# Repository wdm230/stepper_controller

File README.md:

# Syringe Pump Controller Project

This project provides a complete solution for building a cost-effective syringe pump controller. It includes a C# GUI application for controlling the pump, PCB designs, circuit schematics, 3D printed components, and Arduino code for the ESP32 microcontroller.

## Table of Contents

1. [Introduction](#introduction)
2. [Project Structure](#project-structure)
3. [C# GUI Application](#c-gui-application)
4. [PCB Design](#pcb-design)
5. [Circuit and PCB Files](#circuit-and-pcb-files)
6. [3D Models](#3d-models)
7. [Arduino Code](#arduino-code)
8. [Documentation](#documentation)
9. [How to Contribute](#how-to-contribute)
10. [License](#license)

## Introduction

This project is focused on developing an affordable syringe pump controller that can be assembled with readily available components. The controller is built around an ESP32 microcontroller, with a C# application providing a user-friendly interface. The hardware includes a custom PCB and 3D-printed components to house the electronics and mechanical parts.

## Project Structure

The repository is organized as follows:

- **GUI/**: C# codebase for the graphical user interface (GUI) application.
- **PCB/**: Gerber files for manufacturing the printed circuit board (PCB).
- **circuit_board/**: KiCad project files, including the circuit schematic and PCB layout.
- **models/**: 3D models for printing the syringe pump housing and related parts.
- **syringe_pump_controller.ino**: Arduino sketch for the ESP32 microcontroller, handling motor control and communication with the GUI.
- **docs.pdf**: Comprehensive documentation covering project setup, usage, and technical details.

## C# GUI Application

The C# GUI application provides control over the syringe pump's operation. Key features include:

- Configuring syringe diameter, fluid volume, and flow rate.
- Real-time motor control, including start, stop, and jog functions.
- Monitoring of current syringe position, motor RPM, and estimated time to empty.

The application is developed in C# using .NET, and the source code is located in the `GUI` directory. It can be built using Visual Studio or the .NET CLI.

## PCB Design

The custom PCB integrates the ESP32 microcontroller with the motor driver and other essential components. The Gerber files in the `PCB` directory are ready for submission to any PCB fabrication service.

## Circuit and PCB Files

The `circuit_board` directory contains the KiCad files for the project, including the full circuit schematic and PCB layout. These files are intended for users who need to modify the circuit design or manufacture their own PCBs.

## 3D Models

The `models` directory includes STL files for 3D printing the syringe pump housing and other mechanical parts. These models are designed to fit standard syringe sizes and the custom PCB.

## Arduino Code

The `syringe_pump_controller.ino` file is the Arduino code that runs on the ESP32. This code handles:

- Motor control, including speed, direction, and position tracking.
- Communication with the C# GUI over serial.
- Homing and emergency stop functions.

The code is designed to be flexible and can be modified for different hardware configurations.

## Documentation

Detailed documentation is available in `docs.pdf`, covering all aspects of the project, from hardware assembly to software configuration. It also includes troubleshooting tips, among other things.

## How to Contribute

Contributions are welcome. If you have improvements or fixes, please fork the repository, make your changes, and submit a pull request. Whether it's code enhancements, bug fixes, or documentation updates, your contributions are appreciated.

## License

This project is licensed under the MIT License. See the `LICENSE` file for more details.

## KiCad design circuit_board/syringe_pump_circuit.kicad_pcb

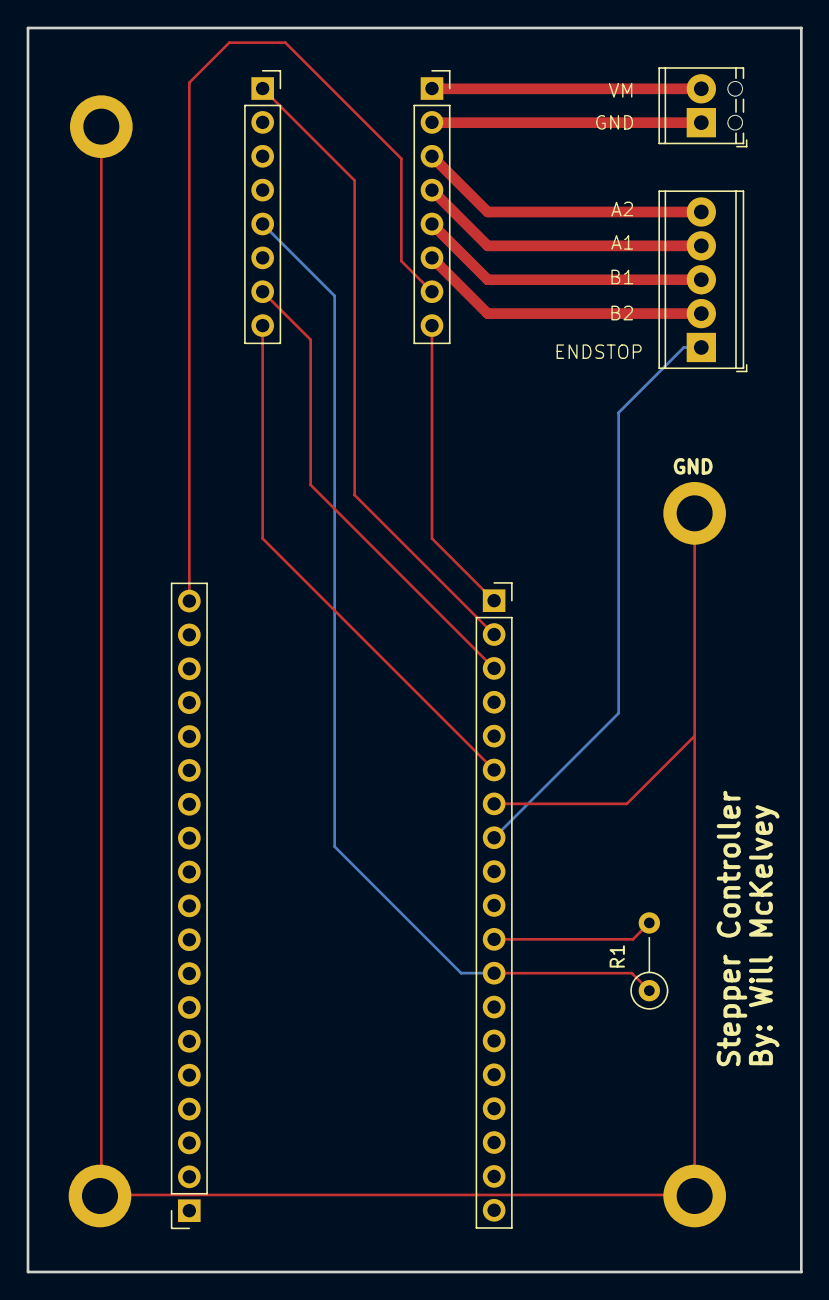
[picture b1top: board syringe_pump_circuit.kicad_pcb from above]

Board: 2 copper layers, 58.0 x 93.3 mm, 11 parts (0 on the bottom side), 15 nets.

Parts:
H1, H2, H3, H4: MountingHole_Pad; MountingHole_2.7mm_M2.5_DIN965_Pad
J1, J2: Conn_01x19_Socket; PinSocket_1x19_P2.54mm_Vertical
J3, J4: Conn_01x08_Socket; PinSocket_1x08_P2.54mm_Vertical
J5: Screw_Terminal_01x05; TerminalBlock_Phoenix_MPT-0,5-5-2.54_1x05_P2.54mm_Horizontal
J6: Screw_Terminal_01x02; TerminalBlock_Phoenix_MPT-0,5-2-2.54_1x02_P2.54mm_Horizontal
R1: 1000; R_Axial_DIN0207_L6.3mm_D2.5mm_P5.08mm_Vertical

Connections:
unnamed: J1.19, J3.7
unnamed: J2.1, J3.8
unnamed: J2.2, J4.1
unnamed: J2.3, J4.7
unnamed: J2.6, J4.8
unnamed: H1.1, H2.1, H3.1, H4.1, J2.7
unnamed: J2.8, J5.1
unnamed: J2.11, R1.2
unnamed: J2.12, J4.5, R1.1
unnamed: J3.1, J6.2
unnamed: J3.2, J6.1
unnamed: J3.3, J5.5
unnamed: J3.4, J5.4
unnamed: J3.5, J5.3
unnamed: J3.6, J5.2

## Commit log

2024-08-15 Add .gitattributes, README.md, and LICENSE.txt.
2024-08-15 Add project files.
2024-08-15 v1.0.0
2024-08-16 added icon
2024-08-16 updated icon
2024-08-17 updated jogging acceleration values
2024-08-17 updated button turn on/off fixed estop error
2024-08-17 commented out some stuff
